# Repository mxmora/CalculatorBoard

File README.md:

# CalculatorBoard
Sample project for a calculator project
From a post on reddit

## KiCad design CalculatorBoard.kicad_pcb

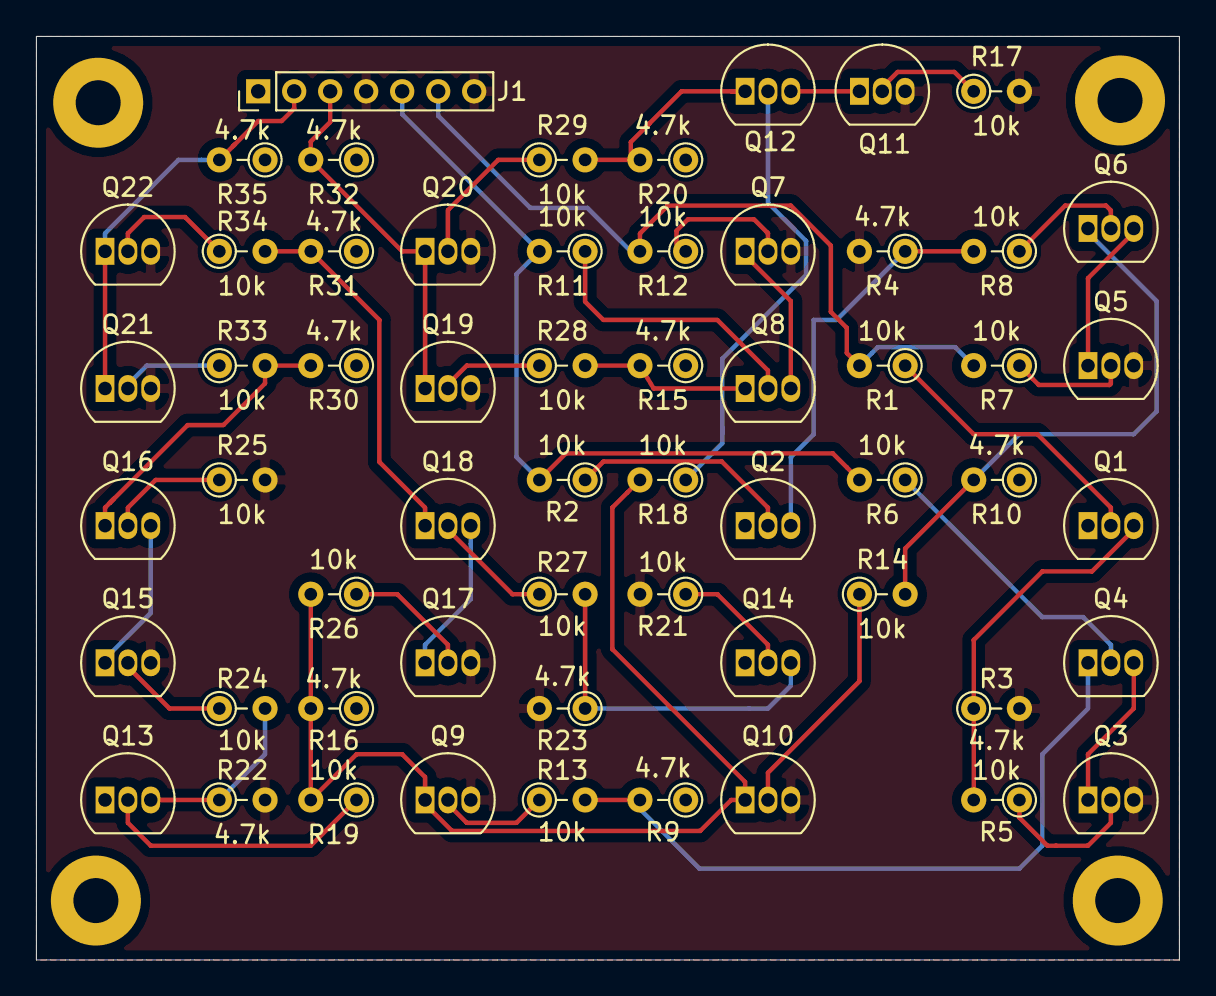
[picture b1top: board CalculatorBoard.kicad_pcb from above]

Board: 2 copper layers, 63.5 x 51.3 mm, 62 parts (0 on the bottom side), 45 nets.

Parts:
H1, H2, H3, H4: MountingHole_Pad; MountingHole_2.5mm_Pad
J1: Conn_01x07_Male; PinHeader_1x07_P2.00mm_Vertical
Q1, Q2, Q3, Q4, Q5, Q6, Q7, Q8, Q9, Q10, Q11, Q12, Q13, Q14, Q15, Q16, Q17, Q18, Q19, Q20, Q21, Q22: Q_NPN_EBC; TO-92_Inline
R1, R2, R5, R6, R7, R8, R11, R12, R13, R14, R17, R18, R19, R21, R24, R25, R26, R27, R28, R29, R33, R34: 10k; R_Axial_DIN0204_L3.6mm_D1.6mm_P2.54mm_Vertical
R3, R4, R9, R10, R15, R16, R20, R22, R23, R30, R31, R32, R35: 4.7k; R_Axial_DIN0204_L3.6mm_D1.6mm_P2.54mm_Vertical

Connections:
2: J1.2, Q21.1, Q22.1, R35.2
3: J1.3, Q19.1, Q20.1, R32.2
6: J1.4, J1.7, Q3.3, Q5.3, Q7.3, Q9.3, Q10.3, Q11.3, Q15.3, Q17.3, Q19.3, Q20.3, Q21.3, Q22.3, R3.2, R4.2, R17.2, R21.2, R22.2, R23.2, R25.2
GND: H1.1, H2.1, H3.1, H4.1, J1.1, Q1.1, Q2.1, Q13.1, Q14.1, R9.1, R10.1, R15.1, R16.1, R20.1, R30.1, R31.1, R32.1, R35.1
unnamed: J1.5, R2.2, R6.2, R11.2
unnamed: J1.6, R1.2, R7.2, R12.2
unnamed: Q1.2, R1.1
unnamed: Q1.3, R3.1, R5.2
unnamed: Q2.2, R2.1
unnamed: Q2.3, R4.1, R8.2
unnamed: Q3.1, Q4.3
unnamed: Q3.2, R5.1
unnamed: Q4.1, R9.2, R13.2
unnamed: Q4.2, R6.1
unnamed: Q5.1, Q6.3
unnamed: Q5.2, R7.1
unnamed: Q6.1, R10.2, R14.2
unnamed: Q6.2, R8.1
unnamed: Q7.1, Q8.3
unnamed: Q7.2, R12.1
unnamed: Q8.1, R15.2, R28.2
unnamed: Q8.2, R11.1
unnamed: Q9.2, R13.1
unnamed: Q9.1, Q10.1, R16.2, R18.2, R19.2, R26.2
unnamed: Q10.2, R14.1
unnamed: Q11.1, Q12.3
unnamed: Q11.2, R17.1
unnamed: Q12.1, R20.2, R29.2
unnamed: Q12.2, R18.1
unnamed: Q13.2, R19.1
unnamed: Q13.3, R22.1, R24.2
unnamed: Q14.2, R21.1
unnamed: Q14.3, R23.1, R27.2
unnamed: Q15.1, Q16.3
unnamed: Q15.2, R24.1
unnamed: Q16.1, R30.2, R33.2
unnamed: Q16.2, R25.1
unnamed: Q17.1, Q18.3
unnamed: Q17.2, R26.1
unnamed: Q18.1, R31.2, R34.2
unnamed: Q18.2, R27.1
unnamed: Q19.2, R28.1
unnamed: Q20.2, R29.1
unnamed: Q21.2, R33.1
unnamed: Q22.2, R34.1

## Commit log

2019-06-13 check in files
2019-06-14 fix pin 5 goof. Reroute some components.
2019-06-14 change resistor size and shrink layout
2019-06-15 minor tweaks
2019-06-15 clean up some traces
